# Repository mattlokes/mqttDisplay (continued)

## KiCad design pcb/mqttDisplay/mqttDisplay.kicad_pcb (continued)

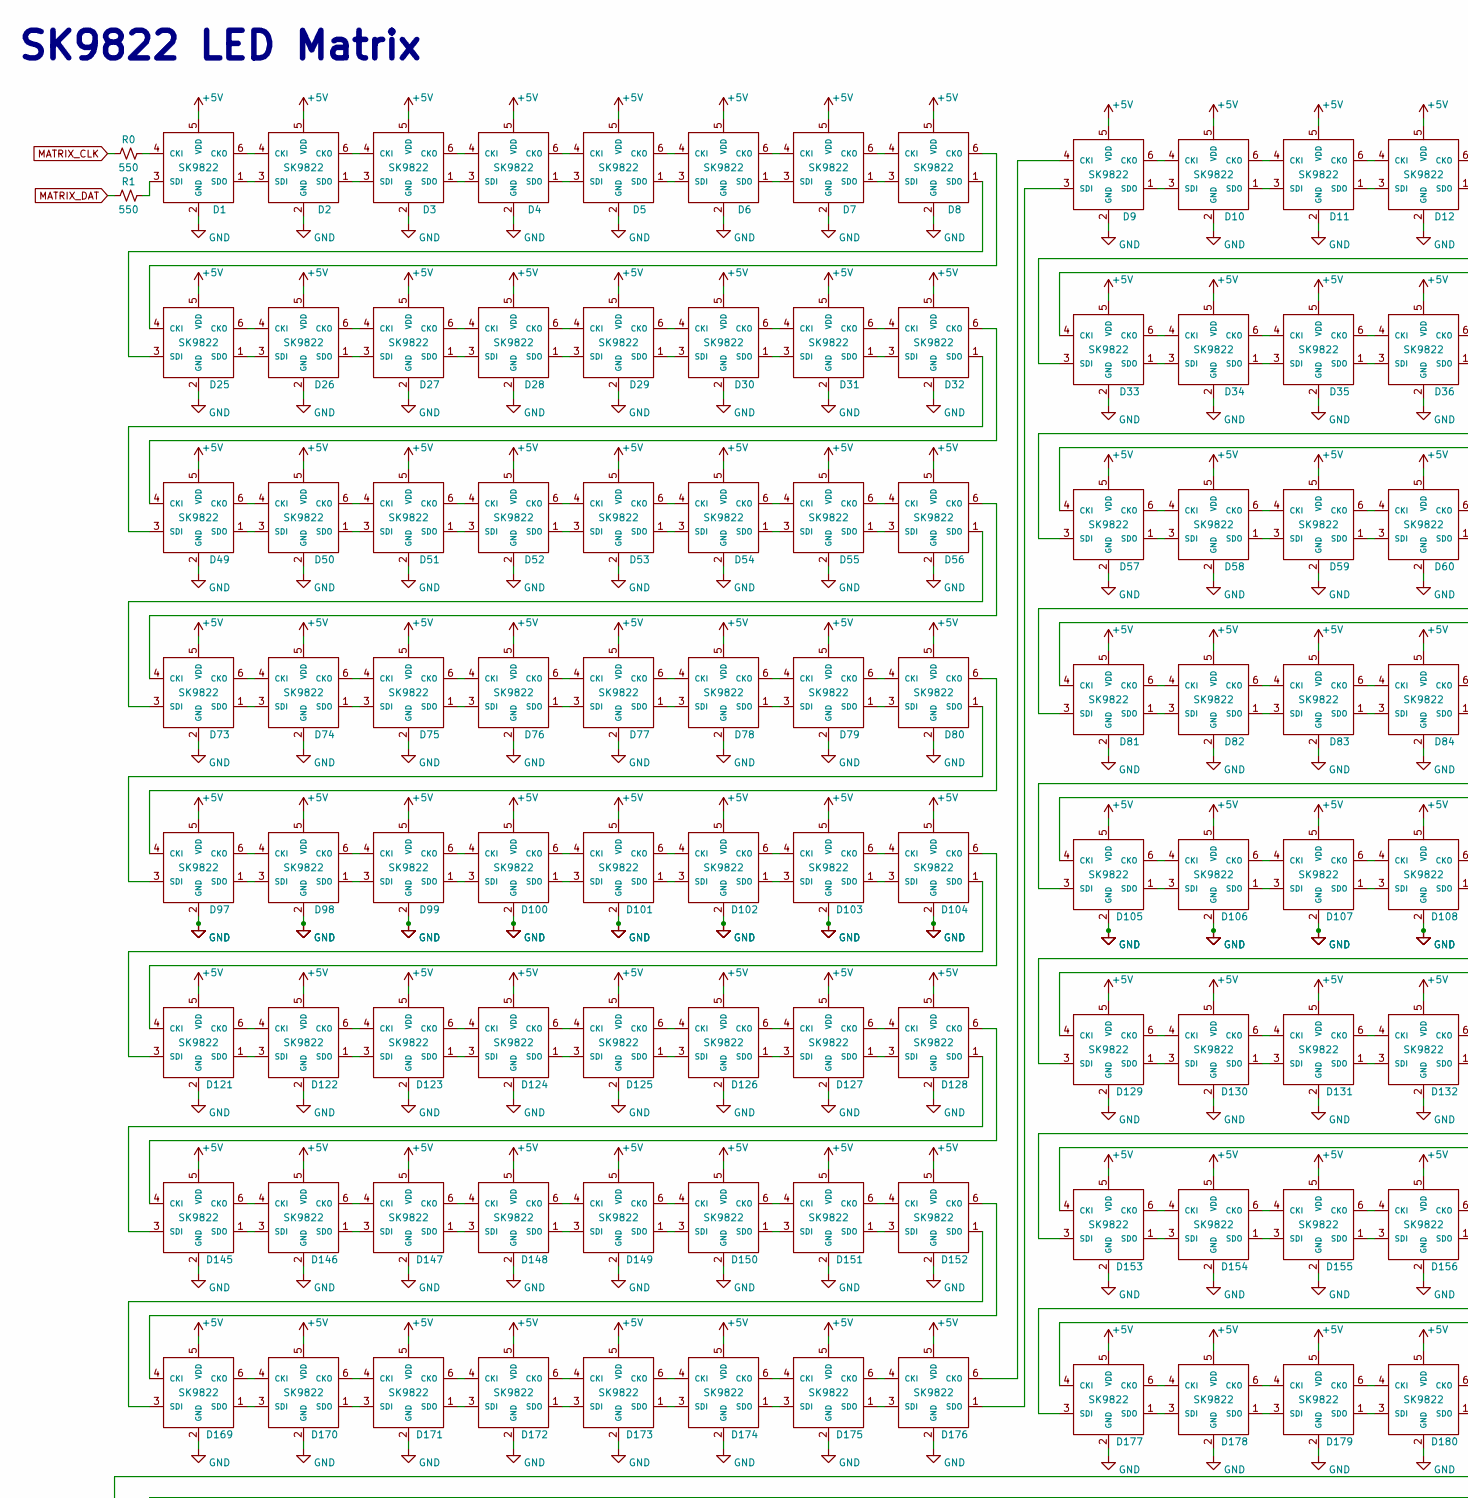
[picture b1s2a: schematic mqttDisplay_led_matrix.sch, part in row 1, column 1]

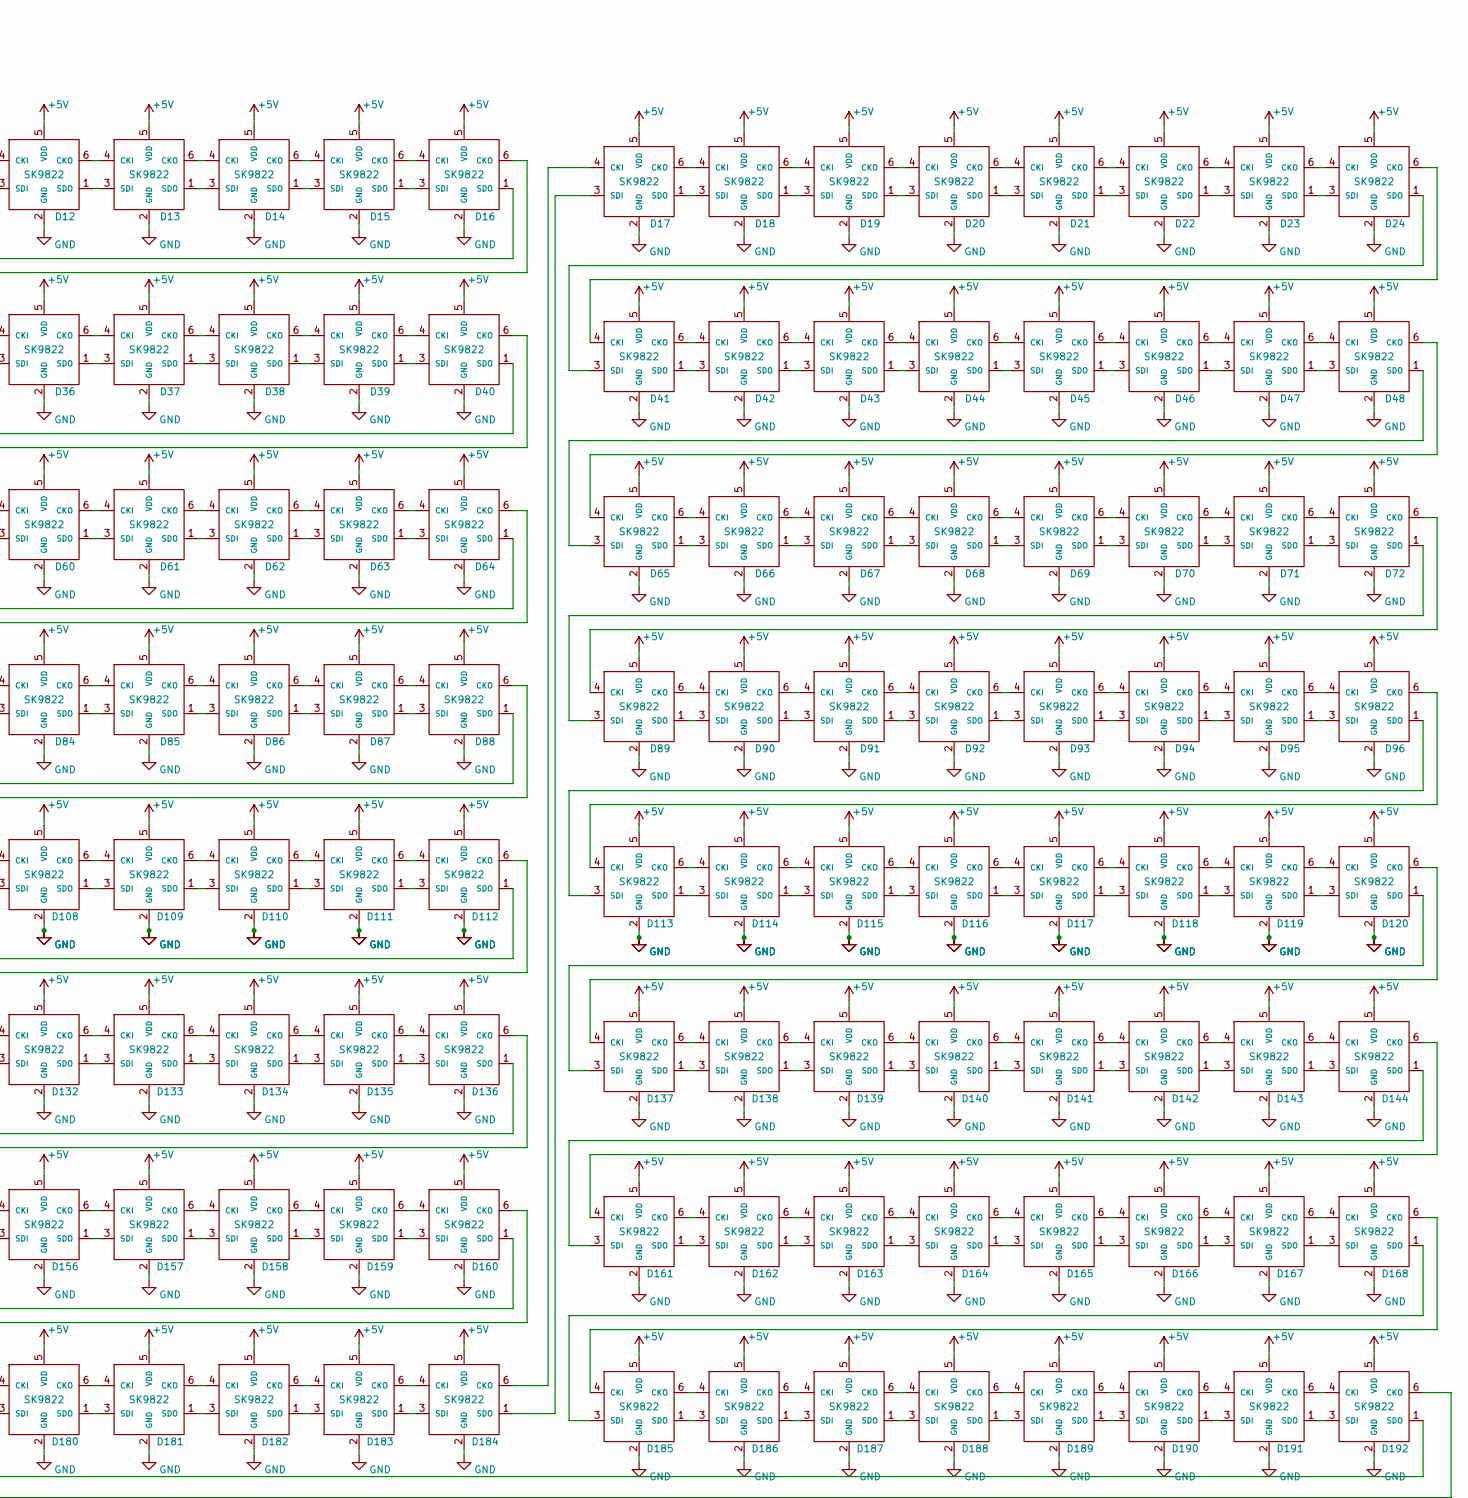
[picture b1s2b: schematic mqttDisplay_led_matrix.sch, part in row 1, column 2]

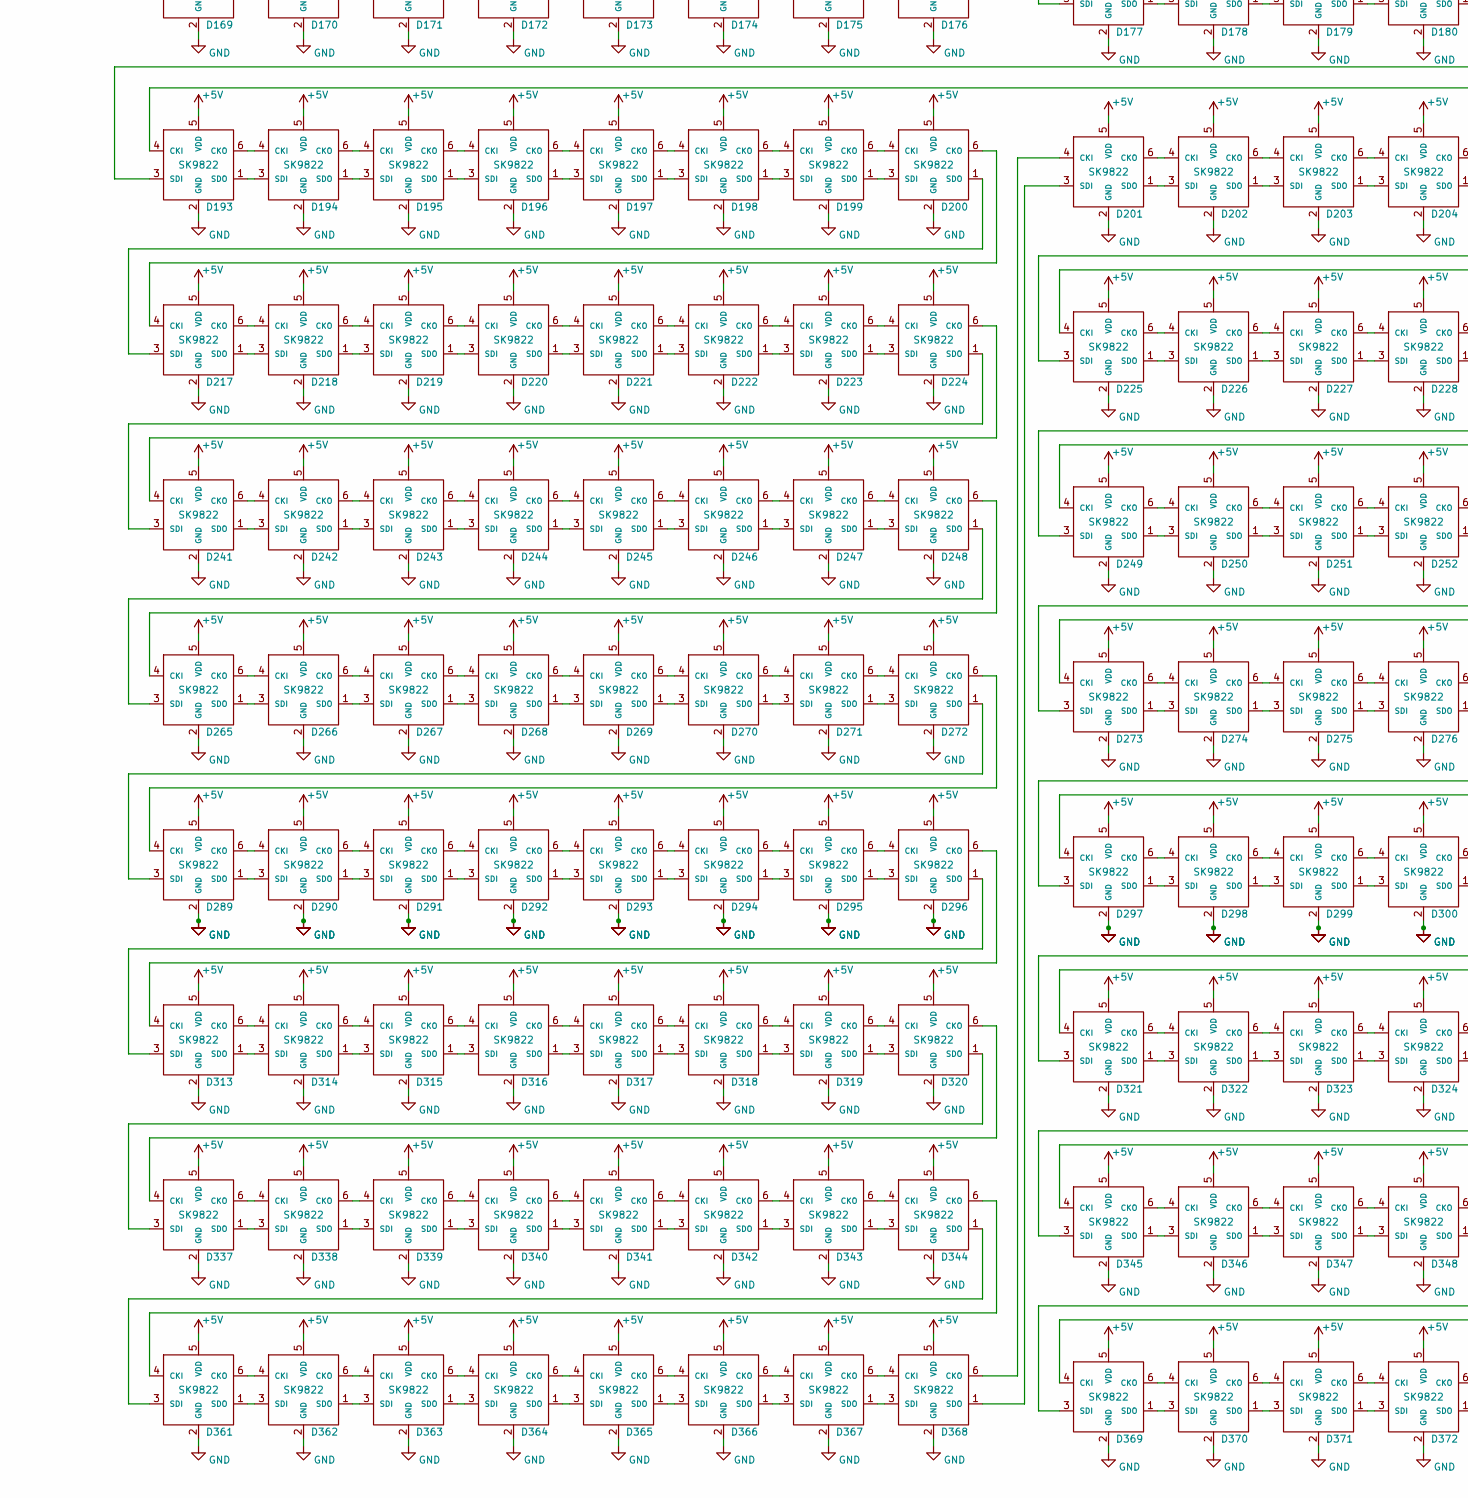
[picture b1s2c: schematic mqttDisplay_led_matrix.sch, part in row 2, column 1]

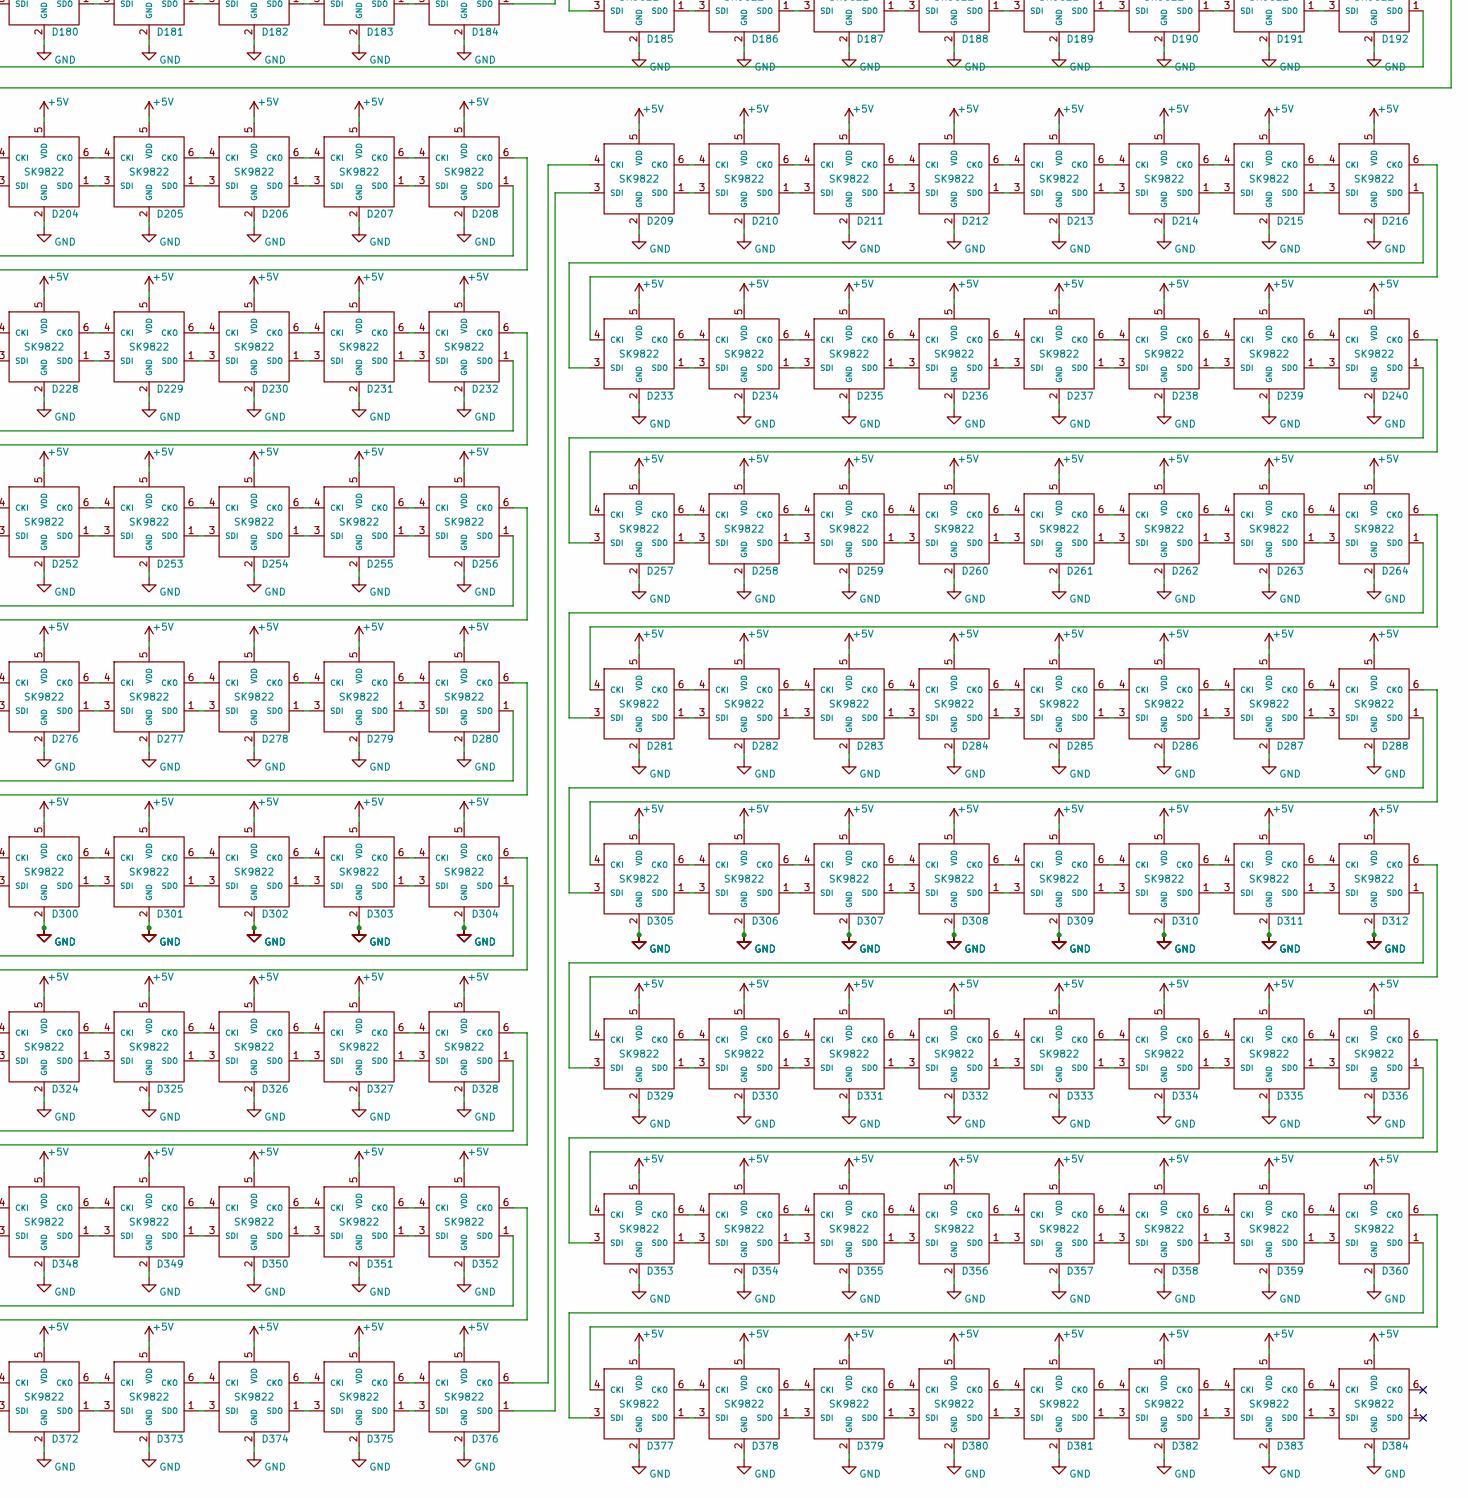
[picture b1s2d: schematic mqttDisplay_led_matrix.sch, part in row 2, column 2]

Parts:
D1, D2, D3, D4, D5, D6, D7, D8, D9, D10, D11, D12, D13, D14, D15, D16, D17, D18, D19, D20, D21, D22, D23, D24, D25, D26, D27, D28, D29, D30, D31, D32, D33, D34, D35, D36, D37, D38, D39, D40, D41, D42, D43, D44, D45, D46, D47, D48, D49, D50, D51, D52, D53, D54, D55, D56, D57, D58, D59, D60, D61, D62, D63, D64, D65, D66, D67, D68, D69, D70, D71, D72, D73, D74, D75, D76, D77, D78, D79, D80, D81, D82, D83, D84, D85, D86, D87, D88, D89, D90, D91, D92, D93, D94, D95, D96, D97, D98, D99, D100, D101, D102, D103, D104, D105, D106, D107, D108, D109, D110, D111, D112, D113, D114, D115, D116, D117, D118, D119, D120, D121, D122, D123, D124, D125, D126, D127, D128, D129, D130, D131, D132, D133, D134, D135, D136, D137, D138, D139, D140, D141, D142, D143, D144, D145, D146, D147, D148, D149, D150, D151, D152, D153, D154, D155, D156, D157, D158, D159, D160, D161, D162, D163, D164, D165, D166, D167, D168, D169, D170, D171, D172, D173, D174, D175, D176, D177, D178, D179, D180, D181, D182, D183, D184, D185, D186, D187, D188, D189, D190, D191, D192, D193, D194, D195, D196, D197, D198, D199, D200, D201, D202, D203, D204, D205, D206, D207, D208, D209, D210, D211, D212, D213, D214, D215, D216, D217, D218, D219, D220, D221, D222, D223, D224, D225, D226, D227, D228, D229, D230, D231, D232, D233, D234, D235, D236, D237, D238, D239, D240, D241, D242, D243, D244, D245, D246, D247, D248, D249, D250, D251, D252, D253, D254, D255, D256, D257, D258, D259, D260, D261, D262, D263, D264, D265, D266, D267, D268, D269, D270, D271, D272, D273, D274, D275, D276, D277, D278, D279, D280, D281, D282, D283, D284, D285, D286, D287, D288, D289, D290, D291, D292, D293, D294, D295, D296, D297, D298, D299, D300, D301, D302, D303, D304, D305, D306, D307, D308, D309, D310, D311, D312, D313, D314, D315, D316, D317, D318, D319, D320, D321, D322, D323, D324, D325, D326, D327, D328, D329, D330, D331, D332, D333, D334, D335, D336, D337, D338, D339, D340, D341, D342, D343, D344, D345, D346, D347, D348, D349, D350, D351, D352, D353, D354, D355, D356, D357, D358, D359, D360, D361, D362, D363, D364, D365, D366, D367, D368, D369, D370, D371, D372, D373, D374, D375, D376, D377, D378, D379, D380, D381, D382, D383, D384: SK9822; LED_SK9822_2020; LCSC# --
R0, R1: 550; R_0603_1608Metric_Pad0.98x0.95mm_HandSolder; LCSC# C308281

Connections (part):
+5V: D1.5 (VDD), D2.5 (VDD), D3.5 (VDD), D4.5 (VDD), D5.5 (VDD), D6.5 (VDD), D7.5 (VDD), D8.5 (VDD), D9.5 (VDD), D10.5 (VDD), D11.5 (VDD), D12.5 (VDD), D13.5 (VDD), D14.5 (VDD), D15.5 (VDD), D16.5 (VDD), D17.5 (VDD), D18.5 (VDD), D19.5 (VDD), D20.5 (VDD), D21.5 (VDD), D22.5 (VDD), D23.5 (VDD), D24.5 (VDD), D25.5 (VDD), D26.5 (VDD), D27.5 (VDD), D28.5 (VDD), D29.5 (VDD), D30.5 (VDD), D31.5 (VDD), D32.5 (VDD), D33.5 (VDD), D34.5 (VDD), D35.5 (VDD), D36.5 (VDD), D37.5 (VDD), D38.5 (VDD), D39.5 (VDD), D40.5 (VDD), D41.5 (VDD), D42.5 (VDD), D43.5 (VDD), D44.5 (VDD), D45.5 (VDD), D46.5 (VDD), D47.5 (VDD), D48.5 (VDD), D49.5 (VDD), D50.5 (VDD), D51.5 (VDD), D52.5 (VDD), D53.5 (VDD), D54.5 (VDD), D55.5 (VDD), D56.5 (VDD), D57.5 (VDD), D58.5 (VDD), D59.5 (VDD), D60.5 (VDD), D61.5 (VDD), D62.5 (VDD), D63.5 (VDD), D64.5 (VDD), D65.5 (VDD), D66.5 (VDD), D67.5 (VDD), D68.5 (VDD), D69.5 (VDD), D70.5 (VDD), D71.5 (VDD), D72.5 (VDD), D73.5 (VDD), D74.5 (VDD), D75.5 (VDD), D76.5 (VDD), D77.5 (VDD), D78.5 (VDD), D79.5 (VDD), D80.5 (VDD)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; also elsewhere on the board
GND: D1.2 (GND), D2.2 (GND), D3.2 (GND), D4.2 (GND), D5.2 (GND), D6.2 (GND), D7.2 (GND), D8.2 (GND), D9.2 (GND), D10.2 (GND), D11.2 (GND), D12.2 (GND), D13.2 (GND), D14.2 (GND), D15.2 (GND), D16.2 (GND), D17.2 (GND), D18.2 (GND), D19.2 (GND), D20.2 (GND), D21.2 (GND), D22.2 (GND), D23.2 (GND), D24.2 (GND), D25.2 (GND), D26.2 (GND), D27.2 (GND), D28.2 (GND), D29.2 (GND), D30.2 (GND), D31.2 (GND), D32.2 (GND), D33.2 (GND), D34.2 (GND), D35.2 (GND), D36.2 (GND), D37.2 (GND), D38.2 (GND), D39.2 (GND), D40.2 (GND), D41.2 (GND), D42.2 (GND), D43.2 (GND), D44.2 (GND), D45.2 (GND), D46.2 (GND), D47.2 (GND), D48.2 (GND), D49.2 (GND), D50.2 (GND), D51.2 (GND), D52.2 (GND), D53.2 (GND), D54.2 (GND), D55.2 (GND), D56.2 (GND), D57.2 (GND), D58.2 (GND), D59.2 (GND), D60.2 (GND), D61.2 (GND), D62.2 (GND), D63.2 (GND), D64.2 (GND), D65.2 (GND), D66.2 (GND), D67.2 (GND), D68.2 (GND), D69.2 (GND), D70.2 (GND), D71.2 (GND), D72.2 (GND), D73.2 (GND), D74.2 (GND), D75.2 (GND), D76.2 (GND), D77.2 (GND), D78.2 (GND), D79.2 (GND), D80.2 (GND)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; also elsewhere on the board
MATRIX_CLK: R0.2; also elsewhere on the board
MATRIX_DAT: R1.2; also elsewhere on the board
unnamed: D1.1 (SDO), D2.3 (SDI)
unnamed: D1.3 (SDI), R1.1
unnamed: D1.4 (CKI), R0.1
unnamed: D1.6 (CKO), D2.4 (CKI)
unnamed: D2.1 (SDO), D3.3 (SDI)
unnamed: D2.6 (CKO), D3.4 (CKI)
unnamed: D3.1 (SDO), D4.3 (SDI)
unnamed: D3.6 (CKO), D4.4 (CKI)
unnamed: D4.1 (SDO), D5.3 (SDI)
unnamed: D4.6 (CKO), D5.4 (CKI)
unnamed: D5.1 (SDO), D6.3 (SDI)
unnamed: D5.6 (CKO), D6.4 (CKI)
unnamed: D6.1 (SDO), D7.3 (SDI)
unnamed: D6.6 (CKO), D7.4 (CKI)
unnamed: D7.1 (SDO), D8.3 (SDI)
unnamed: D7.6 (CKO), D8.4 (CKI)
unnamed: D10.1 (SDO), D11.3 (SDI)
unnamed: D9.1 (SDO), D10.3 (SDI)
unnamed: D9.6 (CKO), D10.4 (CKI)
unnamed: D10.6 (CKO), D11.4 (CKI)
unnamed: D11.1 (SDO), D12.3 (SDI)
unnamed: D11.6 (CKO), D12.4 (CKI)
unnamed: D12.1 (SDO), D13.3 (SDI)
unnamed: D12.6 (CKO), D13.4 (CKI)
unnamed: D13.1 (SDO), D14.3 (SDI)
unnamed: D13.6 (CKO), D14.4 (CKI)
unnamed: D14.1 (SDO), D15.3 (SDI)
unnamed: D14.6 (CKO), D15.4 (CKI)
unnamed: D15.1 (SDO), D16.3 (SDI)
unnamed: D15.6 (CKO), D16.4 (CKI)
unnamed: D16.1 (SDO), D33.3 (SDI)
unnamed: D16.6 (CKO), D33.4 (CKI)
unnamed: D17.1 (SDO), D18.3 (SDI)
unnamed: D17.3 (SDI), D184.1 (SDO)
unnamed: D17.4 (CKI), D184.6 (CKO)
unnamed: D17.6 (CKO), D18.4 (CKI)
unnamed: D18.1 (SDO), D19.3 (SDI)
unnamed: D18.6 (CKO), D19.4 (CKI)
unnamed: D19.1 (SDO), D20.3 (SDI)
unnamed: D19.6 (CKO), D20.4 (CKI)
unnamed: D20.1 (SDO), D21.3 (SDI)
unnamed: D20.6 (CKO), D21.4 (CKI)
unnamed: D21.1 (SDO), D22.3 (SDI)
unnamed: D21.6 (CKO), D22.4 (CKI)
unnamed: D22.1 (SDO), D23.3 (SDI)
unnamed: D22.6 (CKO), D23.4 (CKI)
unnamed: D23.1 (SDO), D24.3 (SDI)
unnamed: D23.6 (CKO), D24.4 (CKI)
unnamed: D24.1 (SDO), D41.3 (SDI)
unnamed: D24.6 (CKO), D41.4 (CKI)
unnamed: D25.1 (SDO), D26.3 (SDI)
unnamed: D8.1 (SDO), D25.3 (SDI)
unnamed: D8.6 (CKO), D25.4 (CKI)
unnamed: D25.6 (CKO), D26.4 (CKI)
unnamed: D26.1 (SDO), D27.3 (SDI)
unnamed: D26.6 (CKO), D27.4 (CKI)
unnamed: D27.1 (SDO), D28.3 (SDI)
unnamed: D27.6 (CKO), D28.4 (CKI)
unnamed: D28.1 (SDO), D29.3 (SDI)
unnamed: D28.6 (CKO), D29.4 (CKI)
unnamed: D29.1 (SDO), D30.3 (SDI)
unnamed: D29.6 (CKO), D30.4 (CKI)
unnamed: D30.1 (SDO), D31.3 (SDI)
unnamed: D30.6 (CKO), D31.4 (CKI)
unnamed: D31.1 (SDO), D32.3 (SDI)
unnamed: D31.6 (CKO), D32.4 (CKI)
unnamed: D32.1 (SDO), D49.3 (SDI)
unnamed: D32.6 (CKO), D49.4 (CKI)
unnamed: D33.1 (SDO), D34.3 (SDI)
unnamed: D33.6 (CKO), D34.4 (CKI)
unnamed: D34.1 (SDO), D35.3 (SDI)
unnamed: D34.6 (CKO), D35.4 (CKI)
unnamed: D35.1 (SDO), D36.3 (SDI)
unnamed: D35.6 (CKO), D36.4 (CKI)
unnamed: D36.1 (SDO), D37.3 (SDI)
unnamed: D36.6 (CKO), D37.4 (CKI)
unnamed: D37.1 (SDO), D38.3 (SDI)
unnamed: D37.6 (CKO), D38.4 (CKI)
unnamed: D38.1 (SDO), D39.3 (SDI)
unnamed: D38.6 (CKO), D39.4 (CKI)
unnamed: D39.1 (SDO), D40.3 (SDI)
unnamed: D39.6 (CKO), D40.4 (CKI)
unnamed: D40.1 (SDO), D57.3 (SDI)
unnamed: D40.6 (CKO), D57.4 (CKI)
unnamed: D41.1 (SDO), D42.3 (SDI)
unnamed: D41.6 (CKO), D42.4 (CKI)
unnamed: D42.1 (SDO), D43.3 (SDI)
unnamed: D42.6 (CKO), D43.4 (CKI)
unnamed: D43.1 (SDO), D44.3 (SDI)
unnamed: D43.6 (CKO), D44.4 (CKI)
unnamed: D44.1 (SDO), D45.3 (SDI)
unnamed: D44.6 (CKO), D45.4 (CKI)
unnamed: D45.1 (SDO), D46.3 (SDI)
unnamed: D45.6 (CKO), D46.4 (CKI)
unnamed: D46.1 (SDO), D47.3 (SDI)
unnamed: D46.6 (CKO), D47.4 (CKI)
unnamed: D47.1 (SDO), D48.3 (SDI)
unnamed: D47.6 (CKO), D48.4 (CKI)
unnamed: D48.1 (SDO), D65.3 (SDI)
unnamed: D48.6 (CKO), D65.4 (CKI)
unnamed: D49.1 (SDO), D50.3 (SDI)
unnamed: D49.6 (CKO), D50.4 (CKI)
unnamed: D50.1 (SDO), D51.3 (SDI)
unnamed: D50.6 (CKO), D51.4 (CKI)
unnamed: D51.1 (SDO), D52.3 (SDI)
unnamed: D51.6 (CKO), D52.4 (CKI)
unnamed: D52.1 (SDO), D53.3 (SDI)
unnamed: D52.6 (CKO), D53.4 (CKI)
unnamed: D53.1 (SDO), D54.3 (SDI)
unnamed: D53.6 (CKO), D54.4 (CKI)
unnamed: D54.1 (SDO), D55.3 (SDI)
unnamed: D54.6 (CKO), D55.4 (CKI)
unnamed: D55.1 (SDO), D56.3 (SDI)
unnamed: D55.6 (CKO), D56.4 (CKI)
unnamed: D56.1 (SDO), D73.3 (SDI)
unnamed: D56.6 (CKO), D73.4 (CKI)
unnamed: D57.1 (SDO), D58.3 (SDI)
unnamed: D57.6 (CKO), D58.4 (CKI)
unnamed: D58.1 (SDO), D59.3 (SDI)
unnamed: D58.6 (CKO), D59.4 (CKI)
unnamed: D59.1 (SDO), D60.3 (SDI)
unnamed: D59.6 (CKO), D60.4 (CKI)
unnamed: D60.1 (SDO), D61.3 (SDI)
unnamed: D60.6 (CKO), D61.4 (CKI)
unnamed: D61.1 (SDO), D62.3 (SDI)
unnamed: D61.6 (CKO), D62.4 (CKI)
unnamed: D62.1 (SDO), D63.3 (SDI)
unnamed: D62.6 (CKO), D63.4 (CKI)
unnamed: D63.1 (SDO), D64.3 (SDI)
unnamed: D63.6 (CKO), D64.4 (CKI)
unnamed: D64.1 (SDO), D81.3 (SDI)
unnamed: D64.6 (CKO), D81.4 (CKI)
unnamed: D65.1 (SDO), D66.3 (SDI)
unnamed: D65.6 (CKO), D66.4 (CKI)
unnamed: D66.1 (SDO), D67.3 (SDI)
unnamed: D66.6 (CKO), D67.4 (CKI)
unnamed: D67.1 (SDO), D68.3 (SDI)
unnamed: D67.6 (CKO), D68.4 (CKI)
unnamed: D68.1 (SDO), D69.3 (SDI)
unnamed: D68.6 (CKO), D69.4 (CKI)
unnamed: D69.1 (SDO), D70.3 (SDI)
unnamed: D69.6 (CKO), D70.4 (CKI)
unnamed: D70.1 (SDO), D71.3 (SDI)
unnamed: D70.6 (CKO), D71.4 (CKI)
unnamed: D71.1 (SDO), D72.3 (SDI)
unnamed: D71.6 (CKO), D72.4 (CKI)
unnamed: D72.1 (SDO), D89.3 (SDI)
unnamed: D72.6 (CKO), D89.4 (CKI)
unnamed: D73.1 (SDO), D74.3 (SDI)
unnamed: D73.6 (CKO), D74.4 (CKI)
unnamed: D74.1 (SDO), D75.3 (SDI)
unnamed: D74.6 (CKO), D75.4 (CKI)
unnamed: D75.1 (SDO), D76.3 (SDI)
unnamed: D75.6 (CKO), D76.4 (CKI)
unnamed: D76.1 (SDO), D77.3 (SDI)
unnamed: D76.6 (CKO), D77.4 (CKI)
unnamed: D77.1 (SDO), D78.3 (SDI)
unnamed: D77.6 (CKO), D78.4 (CKI)
unnamed: D78.1 (SDO), D79.3 (SDI)
unnamed: D78.6 (CKO), D79.4 (CKI)
unnamed: D79.1 (SDO), D80.3 (SDI)
unnamed: D79.6 (CKO), D80.4 (CKI)
unnamed: D80.1 (SDO), D97.3 (SDI)
unnamed: D80.6 (CKO), D97.4 (CKI)
unnamed: D81.1 (SDO), D82.3 (SDI)
unnamed: D81.6 (CKO), D82.4 (CKI)
unnamed: D82.1 (SDO), D83.3 (SDI)
unnamed: D82.6 (CKO), D83.4 (CKI)
unnamed: D83.1 (SDO), D84.3 (SDI)
unnamed: D83.6 (CKO), D84.4 (CKI)
unnamed: D84.1 (SDO), D85.3 (SDI)
unnamed: D84.6 (CKO), D85.4 (CKI)
unnamed: D85.1 (SDO), D86.3 (SDI)
unnamed: D85.6 (CKO), D86.4 (CKI)
unnamed: D86.1 (SDO), D87.3 (SDI)
unnamed: D86.6 (CKO), D87.4 (CKI)
unnamed: D87.1 (SDO), D88.3 (SDI)
unnamed: D87.6 (CKO), D88.4 (CKI)
unnamed: D89.1 (SDO), D90.3 (SDI)
unnamed: D89.6 (CKO), D90.4 (CKI)
unnamed: D90.1 (SDO), D91.3 (SDI)
unnamed: D90.6 (CKO), D91.4 (CKI)
unnamed: D91.1 (SDO), D92.3 (SDI)
unnamed: D91.6 (CKO), D92.4 (CKI)
unnamed: D92.1 (SDO), D93.3 (SDI)
unnamed: D92.6 (CKO), D93.4 (CKI)
unnamed: D93.1 (SDO), D94.3 (SDI)
unnamed: D93.6 (CKO), D94.4 (CKI)
unnamed: D94.1 (SDO), D95.3 (SDI)
unnamed: D94.6 (CKO), D95.4 (CKI)
unnamed: D95.1 (SDO), D96.3 (SDI)
unnamed: D95.6 (CKO), D96.4 (CKI)
unnamed: D97.1 (SDO), D98.3 (SDI)
unnamed: D97.6 (CKO), D98.4 (CKI)
unnamed: D98.1 (SDO), D99.3 (SDI)
unnamed: D98.6 (CKO), D99.4 (CKI)
unnamed: D100.1 (SDO), D101.3 (SDI)
unnamed: D99.1 (SDO), D100.3 (SDI)
unnamed: D99.6 (CKO), D100.4 (CKI)
unnamed: D100.6 (CKO), D101.4 (CKI)
unnamed: D101.1 (SDO), D102.3 (SDI)
unnamed: D101.6 (CKO), D102.4 (CKI)
unnamed: D102.1 (SDO), D103.3 (SDI)
unnamed: D102.6 (CKO), D103.4 (CKI)
unnamed: D103.1 (SDO), D104.3 (SDI)
unnamed: D103.6 (CKO), D104.4 (CKI)
unnamed: D104.1 (SDO), D121.3 (SDI)
unnamed: D104.6 (CKO), D121.4 (CKI)
unnamed: D105.1 (SDO), D106.3 (SDI)
unnamed: D88.1 (SDO), D105.3 (SDI)
unnamed: D88.6 (CKO), D105.4 (CKI)
unnamed: D105.6 (CKO), D106.4 (CKI)
unnamed: D106.1 (SDO), D107.3 (SDI)
unnamed: D106.6 (CKO), D107.4 (CKI)
unnamed: D107.1 (SDO), D108.3 (SDI)
unnamed: D107.6 (CKO), D108.4 (CKI)
unnamed: D108.1 (SDO), D109.3 (SDI)
unnamed: D108.6 (CKO), D109.4 (CKI)
unnamed: D109.1 (SDO), D110.3 (SDI)
unnamed: D109.6 (CKO), D110.4 (CKI)
unnamed: D110.1 (SDO), D111.3 (SDI)
unnamed: D110.6 (CKO), D111.4 (CKI)
unnamed: D111.1 (SDO), D112.3 (SDI)
unnamed: D111.6 (CKO), D112.4 (CKI)
unnamed: D112.1 (SDO), D129.3 (SDI)
unnamed: D112.6 (CKO), D129.4 (CKI)
unnamed: D113.1 (SDO), D114.3 (SDI)
unnamed: D96.1 (SDO), D113.3 (SDI)
unnamed: D96.6 (CKO), D113.4 (CKI)
unnamed: D113.6 (CKO), D114.4 (CKI)
unnamed: D114.1 (SDO), D115.3 (SDI)
unnamed: D114.6 (CKO), D115.4 (CKI)
unnamed: D115.1 (SDO), D116.3 (SDI)
unnamed: D115.6 (CKO), D116.4 (CKI)
unnamed: D116.1 (SDO), D117.3 (SDI)
unnamed: D116.6 (CKO), D117.4 (CKI)
unnamed: D117.1 (SDO), D118.3 (SDI)
unnamed: D117.6 (CKO), D118.4 (CKI)
unnamed: D118.1 (SDO), D119.3 (SDI)
unnamed: D118.6 (CKO), D119.4 (CKI)
unnamed: D119.1 (SDO), D120.3 (SDI)
unnamed: D119.6 (CKO), D120.4 (CKI)
unnamed: D120.1 (SDO), D137.3 (SDI)
unnamed: D120.6 (CKO), D137.4 (CKI)
unnamed: D121.1 (SDO), D122.3 (SDI)
unnamed: D121.6 (CKO), D122.4 (CKI)
unnamed: D122.1 (SDO), D123.3 (SDI)
unnamed: D122.6 (CKO), D123.4 (CKI)
unnamed: D123.1 (SDO), D124.3 (SDI)
unnamed: D123.6 (CKO), D124.4 (CKI)
unnamed: D124.1 (SDO), D125.3 (SDI)
unnamed: D124.6 (CKO), D125.4 (CKI)
unnamed: D125.1 (SDO), D126.3 (SDI)
unnamed: D125.6 (CKO), D126.4 (CKI)
unnamed: D126.1 (SDO), D127.3 (SDI)
unnamed: D126.6 (CKO), D127.4 (CKI)
unnamed: D127.1 (SDO), D128.3 (SDI)
unnamed: D127.6 (CKO), D128.4 (CKI)
unnamed: D128.1 (SDO), D145.3 (SDI)
unnamed: D128.6 (CKO), D145.4 (CKI)
unnamed: D129.1 (SDO), D130.3 (SDI)
unnamed: D129.6 (CKO), D130.4 (CKI)
unnamed: D130.1 (SDO), D131.3 (SDI)
unnamed: D130.6 (CKO), D131.4 (CKI)
unnamed: D131.1 (SDO), D132.3 (SDI)
unnamed: D131.6 (CKO), D132.4 (CKI)
unnamed: D132.1 (SDO), D133.3 (SDI)
unnamed: D132.6 (CKO), D133.4 (CKI)
unnamed: D133.1 (SDO), D134.3 (SDI)
unnamed: D133.6 (CKO), D134.4 (CKI)
unnamed: D134.1 (SDO), D135.3 (SDI)
unnamed: D134.6 (CKO), D135.4 (CKI)
unnamed: D135.1 (SDO), D136.3 (SDI)
unnamed: D135.6 (CKO), D136.4 (CKI)
unnamed: D136.1 (SDO), D153.3 (SDI)
unnamed: D136.6 (CKO), D153.4 (CKI)
unnamed: D137.1 (SDO), D138.3 (SDI)
unnamed: D137.6 (CKO), D138.4 (CKI)
unnamed: D138.1 (SDO), D139.3 (SDI)
unnamed: D138.6 (CKO), D139.4 (CKI)
unnamed: D139.1 (SDO), D140.3 (SDI)
unnamed: D139.6 (CKO), D140.4 (CKI)
unnamed: D140.1 (SDO), D141.3 (SDI)
unnamed: D140.6 (CKO), D141.4 (CKI)
unnamed: D141.1 (SDO), D142.3 (SDI)
unnamed: D141.6 (CKO), D142.4 (CKI)
unnamed: D142.1 (SDO), D143.3 (SDI)
unnamed: D142.6 (CKO), D143.4 (CKI)
unnamed: D143.1 (SDO), D144.3 (SDI)
unnamed: D143.6 (CKO), D144.4 (CKI)
unnamed: D144.1 (SDO), D161.3 (SDI)
unnamed: D144.6 (CKO), D161.4 (CKI)
unnamed: D145.1 (SDO), D146.3 (SDI)
unnamed: D145.6 (CKO), D146.4 (CKI)
unnamed: D146.1 (SDO), D147.3 (SDI)
unnamed: D146.6 (CKO), D147.4 (CKI)
unnamed: D147.1 (SDO), D148.3 (SDI)
unnamed: D147.6 (CKO), D148.4 (CKI)
unnamed: D148.1 (SDO), D149.3 (SDI)
unnamed: D148.6 (CKO), D149.4 (CKI)
unnamed: D149.1 (SDO), D150.3 (SDI)
unnamed: D149.6 (CKO), D150.4 (CKI)
unnamed: D150.1 (SDO), D151.3 (SDI)
unnamed: D150.6 (CKO), D151.4 (CKI)
unnamed: D151.1 (SDO), D152.3 (SDI)
unnamed: D151.6 (CKO), D152.4 (CKI)
unnamed: D152.1 (SDO), D169.3 (SDI)
unnamed: D152.6 (CKO), D169.4 (CKI)
unnamed: D153.1 (SDO), D154.3 (SDI)
unnamed: D153.6 (CKO), D154.4 (CKI)
unnamed: D154.1 (SDO), D155.3 (SDI)
unnamed: D154.6 (CKO), D155.4 (CKI)
unnamed: D155.1 (SDO), D156.3 (SDI)
unnamed: D155.6 (CKO), D156.4 (CKI)
unnamed: D156.1 (SDO), D157.3 (SDI)
unnamed: D156.6 (CKO), D157.4 (CKI)
unnamed: D157.1 (SDO), D158.3 (SDI)
unnamed: D157.6 (CKO), D158.4 (CKI)
unnamed: D158.1 (SDO), D159.3 (SDI)
unnamed: D158.6 (CKO), D159.4 (CKI)
unnamed: D159.1 (SDO), D160.3 (SDI)
unnamed: D159.6 (CKO), D160.4 (CKI)
unnamed: D160.1 (SDO), D177.3 (SDI)
unnamed: D160.6 (CKO), D177.4 (CKI)
unnamed: D161.1 (SDO), D162.3 (SDI)
unnamed: D161.6 (CKO), D162.4 (CKI)
unnamed: D162.1 (SDO), D163.3 (SDI)
unnamed: D162.6 (CKO), D163.4 (CKI)
unnamed: D163.1 (SDO), D164.3 (SDI)
unnamed: D163.6 (CKO), D164.4 (CKI)
unnamed: D164.1 (SDO), D165.3 (SDI)
unnamed: D164.6 (CKO), D165.4 (CKI)
unnamed: D165.1 (SDO), D166.3 (SDI)
unnamed: D165.6 (CKO), D166.4 (CKI)
unnamed: D166.1 (SDO), D167.3 (SDI)
unnamed: D166.6 (CKO), D167.4 (CKI)
unnamed: D167.1 (SDO), D168.3 (SDI)
unnamed: D167.6 (CKO), D168.4 (CKI)
unnamed: D168.1 (SDO), D185.3 (SDI)
unnamed: D168.6 (CKO), D185.4 (CKI)
unnamed: D169.1 (SDO), D170.3 (SDI)
unnamed: D169.6 (CKO), D170.4 (CKI)
unnamed: D170.1 (SDO), D171.3 (SDI)
unnamed: D170.6 (CKO), D171.4 (CKI)
unnamed: D171.1 (SDO), D172.3 (SDI)
unnamed: D171.6 (CKO), D172.4 (CKI)
unnamed: D172.1 (SDO), D173.3 (SDI)
unnamed: D172.6 (CKO), D173.4 (CKI)
unnamed: D173.1 (SDO), D174.3 (SDI)
unnamed: D173.6 (CKO), D174.4 (CKI)
unnamed: D174.1 (SDO), D175.3 (SDI)
unnamed: D174.6 (CKO), D175.4 (CKI)
unnamed: D175.1 (SDO), D176.3 (SDI)
unnamed: D175.6 (CKO), D176.4 (CKI)
unnamed: D9.3 (SDI), D176.1 (SDO)
unnamed: D9.4 (CKI), D176.6 (CKO)
unnamed: D177.1 (SDO), D178.3 (SDI)
unnamed: D177.6 (CKO), D178.4 (CKI)
unnamed: D178.1 (SDO), D179.3 (SDI)
unnamed: D178.6 (CKO), D179.4 (CKI)
unnamed: D179.1 (SDO), D180.3 (SDI)
unnamed: D179.6 (CKO), D180.4 (CKI)
unnamed: D180.1 (SDO), D181.3 (SDI)
unnamed: D180.6 (CKO), D181.4 (CKI)
unnamed: D181.1 (SDO), D182.3 (SDI)
unnamed: D181.6 (CKO), D182.4 (CKI)
unnamed: D182.1 (SDO), D183.3 (SDI)
unnamed: D182.6 (CKO), D183.4 (CKI)
unnamed: D183.1 (SDO), D184.3 (SDI)
unnamed: D183.6 (CKO), D184.4 (CKI)
unnamed: D185.1 (SDO), D186.3 (SDI)
unnamed: D185.6 (CKO), D186.4 (CKI)
unnamed: D186.1 (SDO), D187.3 (SDI)
unnamed: D186.6 (CKO), D187.4 (CKI)
unnamed: D187.1 (SDO), D188.3 (SDI)
unnamed: D187.6 (CKO), D188.4 (CKI)
unnamed: D188.1 (SDO), D189.3 (SDI)
unnamed: D188.6 (CKO), D189.4 (CKI)
unnamed: D189.1 (SDO), D190.3 (SDI)
unnamed: D189.6 (CKO), D190.4 (CKI)
unnamed: D190.1 (SDO), D191.3 (SDI)
unnamed: D190.6 (CKO), D191.4 (CKI)
unnamed: D191.1 (SDO), D192.3 (SDI)
unnamed: D191.6 (CKO), D192.4 (CKI)
unnamed: D192.1 (SDO), D193.3 (SDI)
unnamed: D192.6 (CKO), D193.4 (CKI)
unnamed: D193.1 (SDO), D194.3 (SDI)
unnamed: D193.6 (CKO), D194.4 (CKI)
unnamed: D194.1 (SDO), D195.3 (SDI)
unnamed: D194.6 (CKO), D195.4 (CKI)
unnamed: D195.1 (SDO), D196.3 (SDI)
unnamed: D195.6 (CKO), D196.4 (CKI)
unnamed: D196.1 (SDO), D197.3 (SDI)
unnamed: D196.6 (CKO), D197.4 (CKI)
unnamed: D197.1 (SDO), D198.3 (SDI)
unnamed: D197.6 (CKO), D198.4 (CKI)
unnamed: D198.1 (SDO), D199.3 (SDI)
unnamed: D198.6 (CKO), D199.4 (CKI)
unnamed: D199.1 (SDO), D200.3 (SDI)
unnamed: D199.6 (CKO), D200.4 (CKI)
unnamed: D200.1 (SDO), D217.3 (SDI)
unnamed: D200.6 (CKO), D217.4 (CKI)
unnamed: D201.1 (SDO), D202.3 (SDI)
unnamed: D201.3 (SDI), D368.1 (SDO)
unnamed: D201.4 (CKI), D368.6 (CKO)
unnamed: D201.6 (CKO), D202.4 (CKI)
unnamed: D202.1 (SDO), D203.3 (SDI)
unnamed: D202.6 (CKO), D203.4 (CKI)
unnamed: D203.1 (SDO), D204.3 (SDI)
unnamed: D203.6 (CKO), D204.4 (CKI)
unnamed: D204.1 (SDO), D205.3 (SDI)
unnamed: D204.6 (CKO), D205.4 (CKI)
unnamed: D205.1 (SDO), D206.3 (SDI)
unnamed: D205.6 (CKO), D206.4 (CKI)
unnamed: D206.1 (SDO), D207.3 (SDI)
unnamed: D206.6 (CKO), D207.4 (CKI)
unnamed: D207.1 (SDO), D208.3 (SDI)
unnamed: D207.6 (CKO), D208.4 (CKI)
unnamed: D208.1 (SDO), D225.3 (SDI)
unnamed: D208.6 (CKO), D225.4 (CKI)
unnamed: D209.1 (SDO), D210.3 (SDI)
unnamed: D209.3 (SDI), D376.1 (SDO)
unnamed: D209.4 (CKI), D376.6 (CKO)
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
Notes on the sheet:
SK9822 LED Matrix
